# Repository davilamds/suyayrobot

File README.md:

# suyayrobot
Suyay Universal Robotic Platform

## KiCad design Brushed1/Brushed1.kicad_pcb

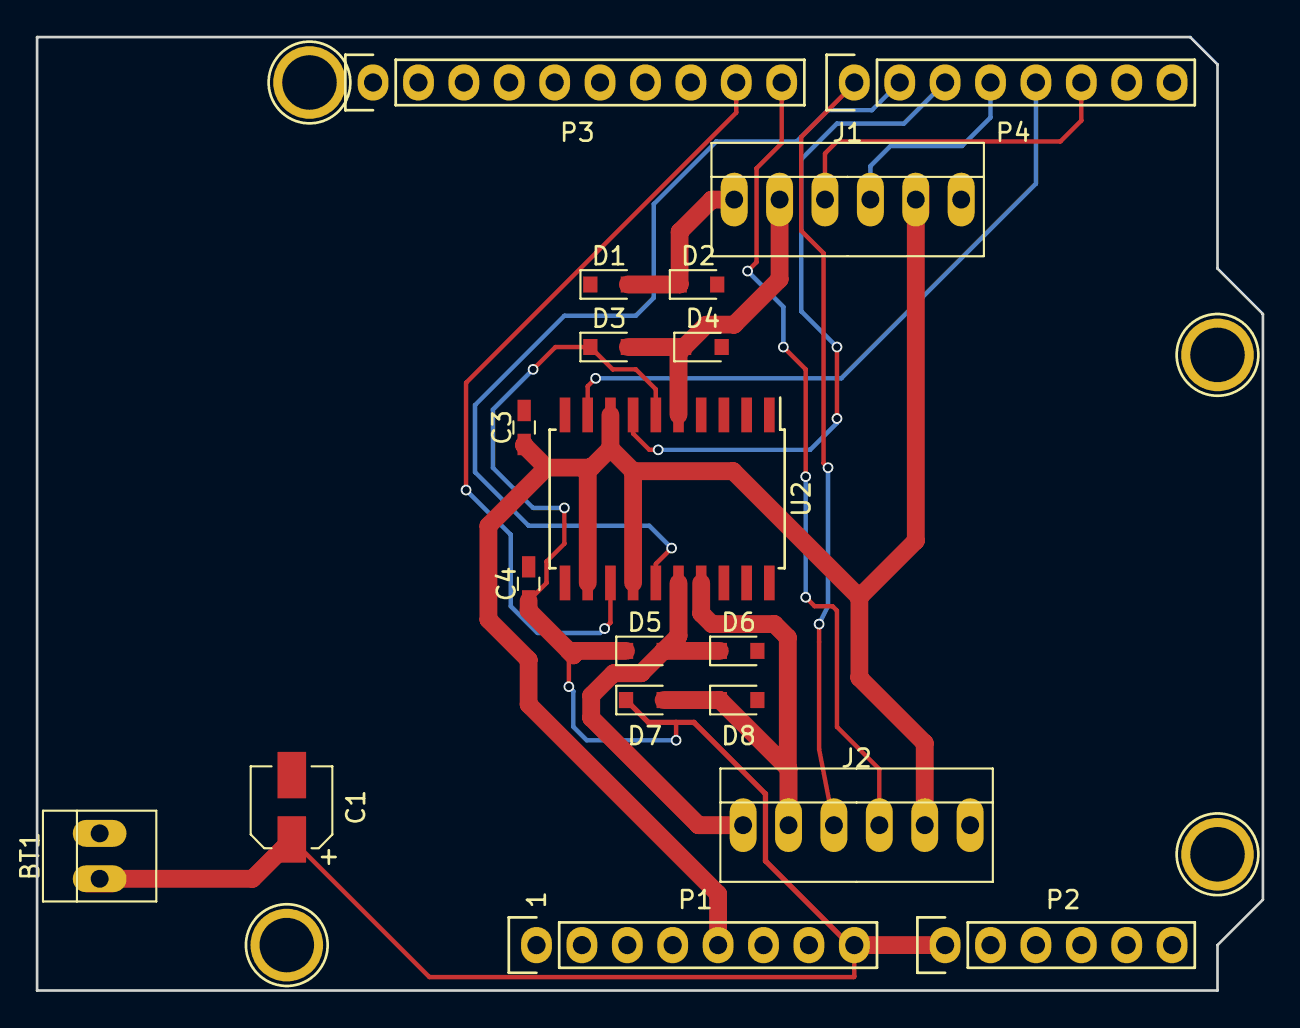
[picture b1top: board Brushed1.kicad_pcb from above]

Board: 2 copper layers, 68.6 x 53.3 mm, 23 parts (0 on the bottom side), 15 nets.

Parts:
BT1: Battery; PINHEAD1-2
C1: 10uF; CP_Elec_4x4.5
C3, C4: 100nF; C_0603_HandSoldering
D1, D2, D3, D4, D5, D6, D7, D8: D; D_0805
J1, J2: CONN_01X06; PINHEAD1-6
P1: Power; Socket_Strip_Arduino_1x08
P2: Analog; Socket_Strip_Arduino_1x06
P3: Digital; Socket_Strip_Arduino_1x10
P4: Digital; Socket_Strip_Arduino_1x08
P5, P6, P7, P8: CONN_01X01; Arduino_1pin
U2: L298P; SOIC-20W_7.5x12.8mm_Pitch1.27mm

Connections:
/2: J1.3, P4.6
/3(**): P4.5, U2.9
/4: J1.4, P4.4
/5(**): P4.3, U2.7
/5.0VCC: C3.1, J1.5, J2.5, P1.5, U2.8, U2.12, U2.14
/6(**): P4.2, U2.15
/7: J2.3, P4.1
/8: J2.4, P3.10
/9(**): P3.9, U2.13
/A0: BT1.1, C1.1, C4.1, D1.1, D3.1, D5.1, D7.1, P1.8, P2.1, U2.6
/M1+: D1.2, D2.1, J1.1, U2.4
/M1-: D3.2, D4.1, J1.2, U2.5
/M2+: D5.2, D6.1, J2.1, U2.16
/M2-: D7.2, D8.1, J2.2, U2.17
GND: BT1.2, C1.2, C3.2, C4.2, D2.2, D4.2, D6.2, D8.2, J1.6, J2.6, P1.6, P1.7, P3.4, U2.1, U2.2, U2.10, U2.11, U2.19, U2.20
